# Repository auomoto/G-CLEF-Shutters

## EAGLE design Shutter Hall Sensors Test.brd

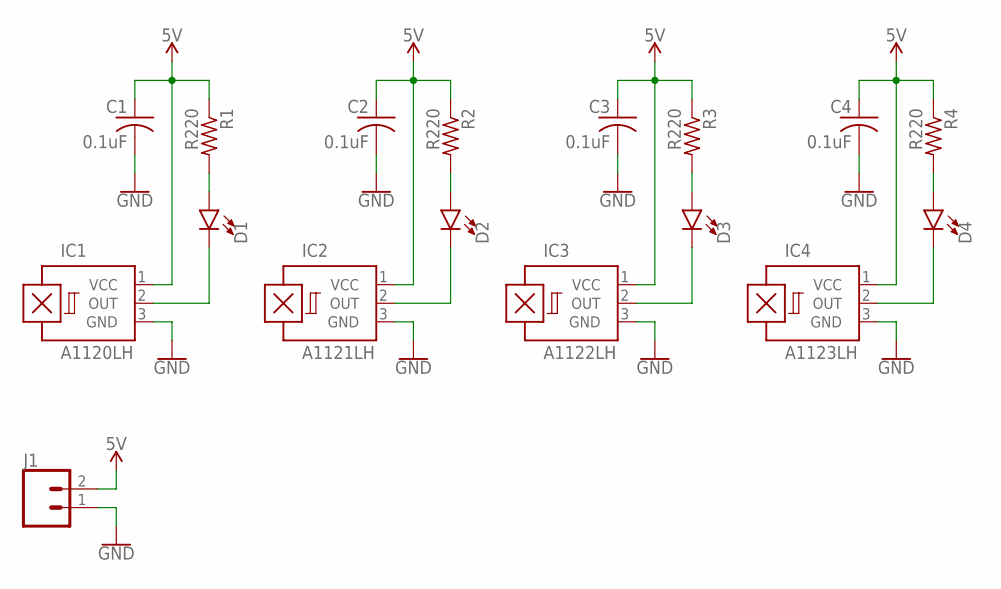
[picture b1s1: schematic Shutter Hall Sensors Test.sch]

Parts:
C1, C2, C3, C4: 0.1uF; C0805
D1, D2, D3, D4: LED5MM; LED_5MM
IC1: A1120LH; SOT23-W
IC2: A1121LH; SOT23-W
IC3: A1122LH; SOT23-W
IC4: A1123LH; SOT23-W
J1: CONN_02; 1X02
R1, R2, R3, R4: R220; R0805

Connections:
5V: C1.1, C2.1, C3.1, C4.1, IC1.1 (VCC), IC2.1 (VCC), IC3.1 (VCC), IC4.1 (VCC), J1.2, R1.1, R2.1, R3.1, R4.1
GND: C1.2, C2.2, C3.2, C4.2, IC1.3 (GND), IC2.3 (GND), IC3.3 (GND), IC4.3 (GND), J1.1
unnamed: D4.A, R4.2
unnamed: D3.K (C), IC3.2 (OUT)
unnamed: D4.K (C), IC4.2 (OUT)
unnamed: D1.A, R1.2
unnamed: D2.K (C), IC2.2 (OUT)
unnamed: D2.A, R2.2
unnamed: D1.K (C), IC1.2 (OUT)
unnamed: D3.A, R3.2

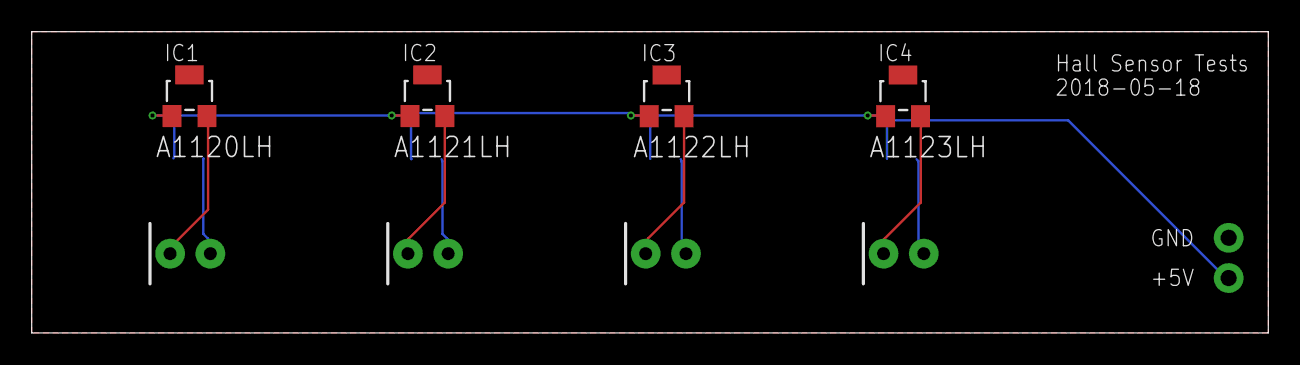
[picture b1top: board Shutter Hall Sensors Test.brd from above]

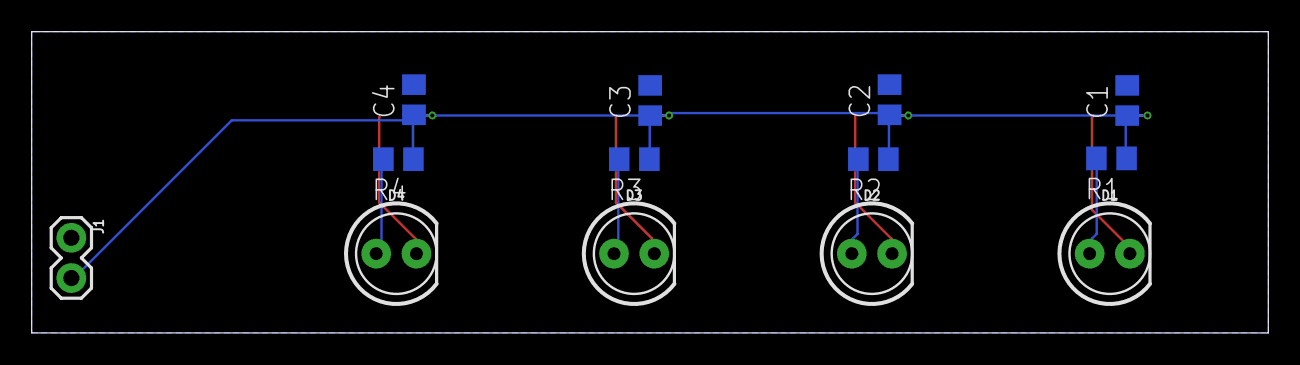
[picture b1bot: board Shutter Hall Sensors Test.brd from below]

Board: 2 copper layers, 78.0 x 19.0 mm, 17 parts (13 on the bottom side), 10 nets.

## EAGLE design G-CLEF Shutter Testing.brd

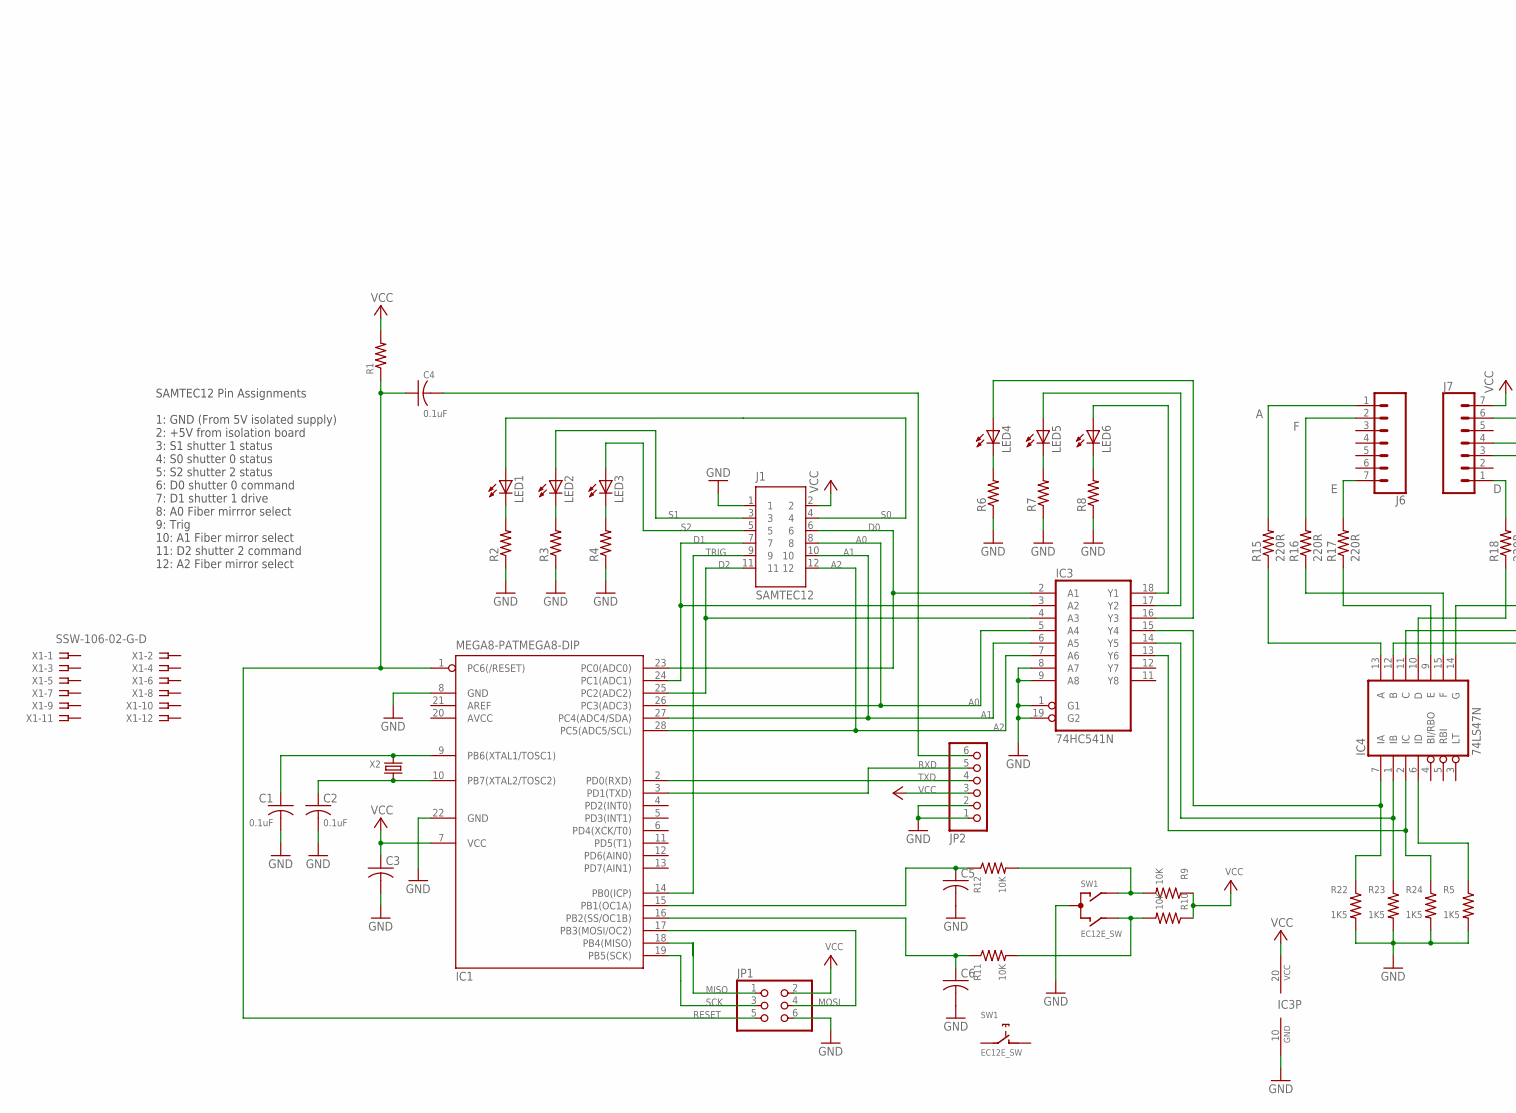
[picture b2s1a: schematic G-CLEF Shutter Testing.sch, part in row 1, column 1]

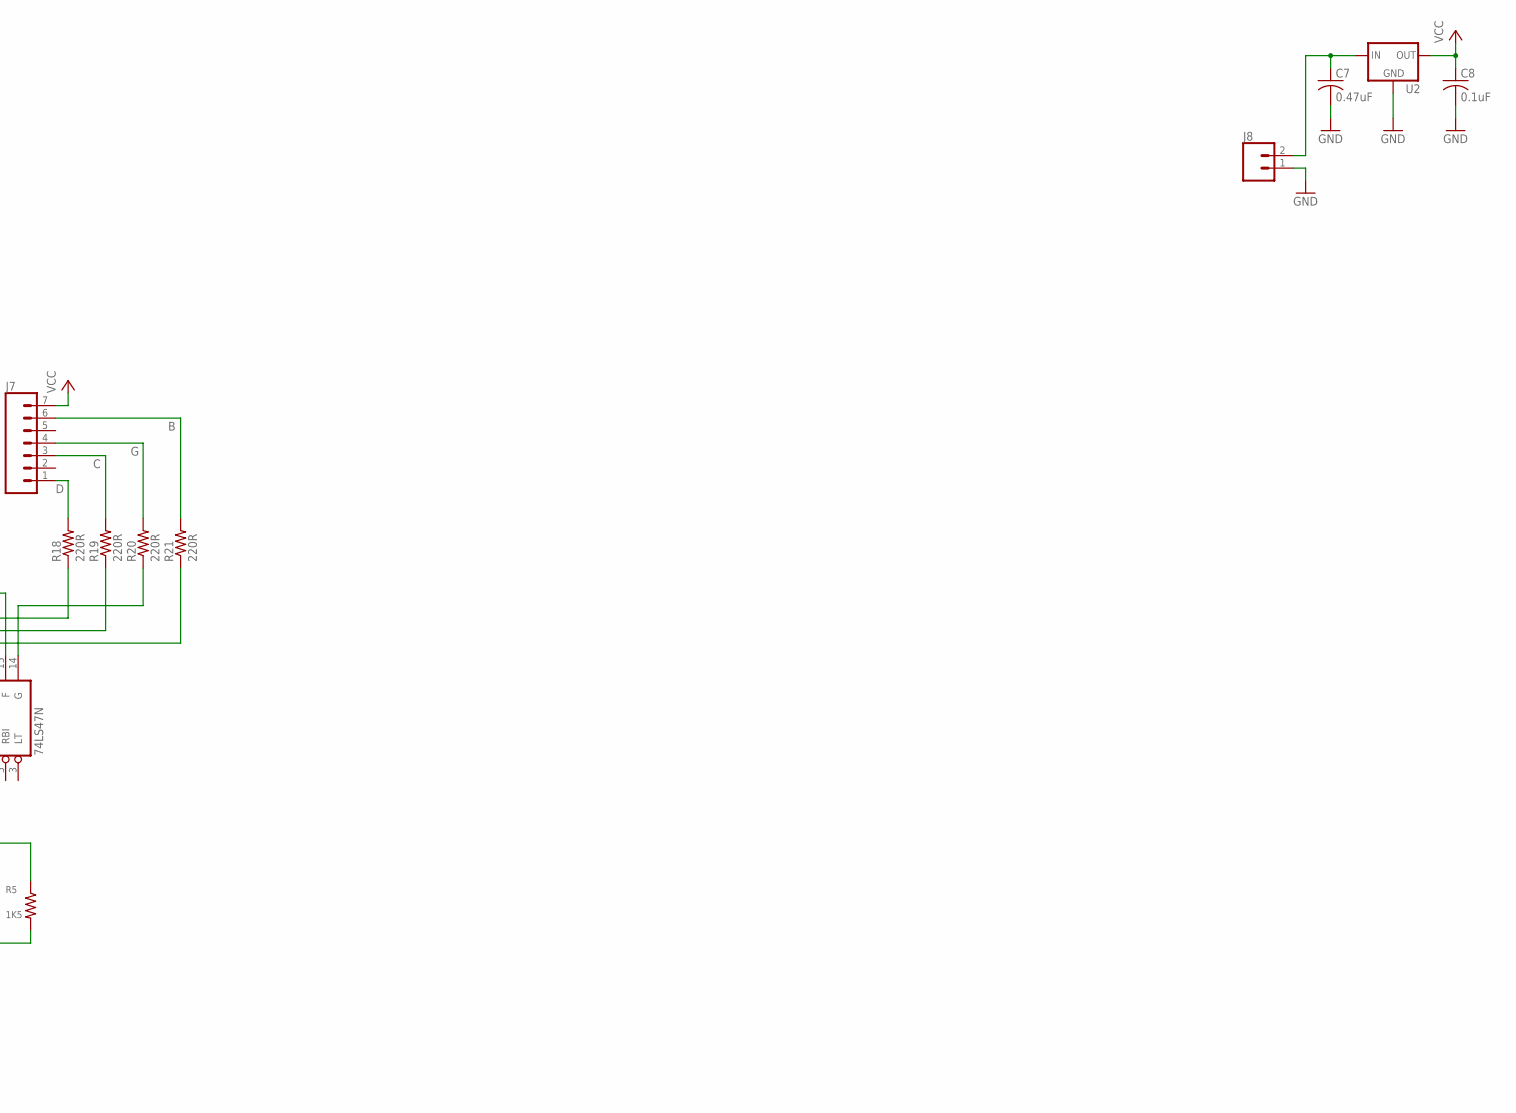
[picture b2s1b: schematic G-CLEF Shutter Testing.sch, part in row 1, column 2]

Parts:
C1, C2, C4: 0.1uF; C025-024X044
C3, C5, C6: C-US025-024X044; C025-024X044
C7: 0.47uF; C050-025X075
C8: 0.1uF; C050-025X075
IC1: MEGA8-PATMEGA8-DIP; DIP762W53P254L3467H457Q28B
IC3: 74HC541N; DIL20
IC4: 74LS47N; DIL16
J1: SAMTEC12
J6, J7: CONN_07; 1X07
J8: CONN_02; 1X02
JP1: PINHD-2X3; 2X03
JP2: PINHD-1X6/90; 1X06/90
LED1, LED2, LED3, LED4, LED5, LED6: LED5MM
R1, R2, R3, R4, R6, R7, R8: R-US_0207/7; 0207/7
R5, R22, R23, R24: 1K5; 0207/7
R9, R10, R11, R12: 10K; 0207/7
R15, R16, R17, R18, R19, R20, R21: 220R; 0207/7
SW1: EC12E_SW; ALPS_EC12E_SW
U2: V_REG_78XXSINK; TO220-IGO
X1: SSW-106-02-G-D
X2: CRYSTALS-NOGND-HC49; HC49

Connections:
A: J6.1, R15.2
A0: IC1.26 (PC3(ADC3)), IC3.5 (A4), J1.8
A1: IC1.27 (PC4(ADC4/SDA)), IC3.6 (A5), J1.10
A2: IC1.28 (PC5(ADC5/SCL)), IC3.7 (A6), J1.12
AVCC: IC1.20 (AVCC)
B: J7.6, R21.2
C: J7.3, R19.2
D: J7.1, R18.2
D0: IC1.23 (PC0(ADC0)), IC3.2 (A1), J1.6
D1: IC1.24 (PC1(ADC1)), IC3.3 (A2), J1.7
D2: IC1.25 (PC2(ADC2)), IC3.4 (A3), J1.11
E: J6.7, R17.2
F: J6.2, R16.2
G: J7.4, R20.2
GND: C1.2, C2.2, C3.2, C5.2, C6.2, C7.2, C8.2, IC1.8 (GND), IC1.22 (GND), IC3.1 (G1), IC3.8 (A7), IC3.9 (A8), IC3.10 (GND), IC3.19 (G2), IC4.8 (GND), J1.1, J8.1, JP1.6, JP2.1, JP2.2, R2.1, R3.1, R4.1, R5.2, R6.1, R7.1, R8.1, R22.2, R23.2, R24.2, SW1.C, U2.GND
MISO: IC1.18 (PB4(MISO)), JP1.1
MOSI: IC1.17 (PB3(MOSI/OC2)), JP1.4
unnamed: C1.1, IC1.9 (PB6(XTAL1/TOSC1)), X2.2
unnamed: C2.1, IC1.10 (PB7(XTAL2/TOSC2)), X2.1
unnamed: C4.2, JP2.6
unnamed: IC4.6 (ID), R5.1
unnamed: LED4.K (C), R6.2
unnamed: LED5.K (C), R7.2
unnamed: LED6.K (C), R8.2
unnamed: IC3.18 (Y1), LED6.A
unnamed: IC3.17 (Y2), LED5.A
unnamed: IC3.16 (Y3), LED4.A
unnamed: C5.1, IC1.15 (PB1(OC1A)), R12.1
unnamed: R9.2, R12.2, SW1.A
unnamed: R10.2, R11.2, SW1.B
unnamed: C6.1, IC1.16 (PB2(SS/OC1B)), R11.1
unnamed: LED1.K (C), R2.2
unnamed: LED2.K (C), R3.2
unnamed: LED3.K (C), R4.2
unnamed: IC4.13 (A), R15.1
unnamed: IC4.12 (B), R21.1
unnamed: IC4.11 (C), R19.1
unnamed: IC4.10 (D), R18.1
unnamed: IC4.9 (E), R17.1
unnamed: IC4.15 (F), R16.1
unnamed: IC4.14 (G), R20.1
unnamed: C7.1, J8.2, U2.IN
unnamed: IC3.13 (Y6), IC4.2 (IC), R24.1
unnamed: IC3.14 (Y5), IC4.1 (IB), R23.1
unnamed: IC3.15 (Y4), IC4.7 (IA), R22.1
RESET: C4.1, IC1.1 (PC6(/RESET)), JP1.5, R1.1
RXD: IC1.3 (PD1(TXD)), JP2.5
S0: J1.4, LED1.A
S1: J1.3, LED2.A
S2: J1.5, LED3.A
SCK: IC1.19 (PB5(SCK)), JP1.3
TRIG: IC1.14 (PB0(ICP)), J1.9
TXD: IC1.2 (PD0(RXD)), JP2.4
VCC: C3.1, C8.1, IC1.7 (VCC), IC3.20 (VCC), IC4.16 (VCC), J1.2, J7.7, JP1.2, JP2.3, R1.2, R9.1, R10.1, U2.OUT

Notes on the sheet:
SAMTEC12 Pin Assignments 1: GND (From 5V isolated supply) 2: +5V from isolation board 3: S1 shutter 1 status 4: S0 shutter 0 status 5: S2 shutter 2 status 6: D0 shutter 0 command 7: D1 shutter 1 drive 8: A0 Fiber mirrror select 9: Trig 10: A1 Fiber mirror select 11: D2 shutter 2 command 12: A2 Fibe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

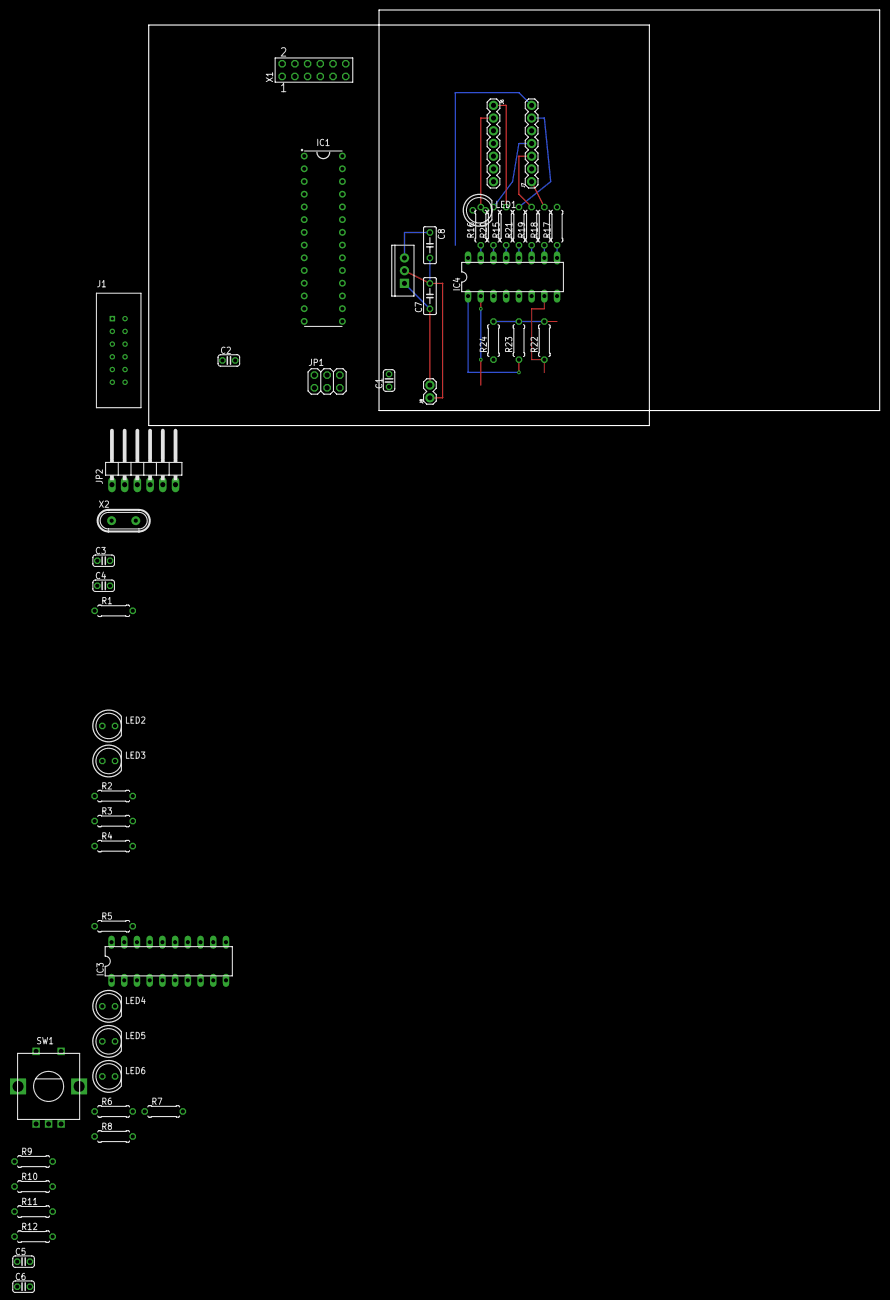
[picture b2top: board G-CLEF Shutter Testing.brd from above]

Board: 2 copper layers, 146.0 x 83.0 mm, 49 parts (0 on the bottom side), 53 nets.

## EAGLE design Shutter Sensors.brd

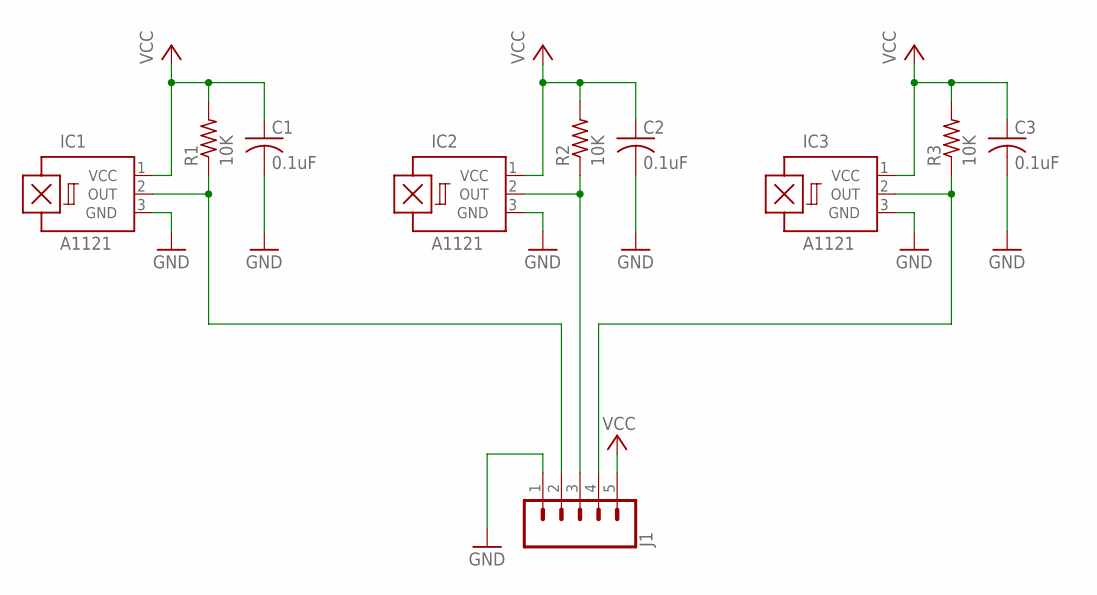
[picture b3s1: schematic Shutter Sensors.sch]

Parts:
C1, C2, C3: 0.1uF; C0805
IC1, IC2, IC3: A1121; SOT95P285X113-3
J1: CONN_051X05-0.1-RA; 1X05/90
R1, R2, R3: 10K; R0805

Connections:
GND: C1.2, C2.2, C3.2, IC1.3 (GND), IC2.3 (GND), IC3.3 (GND), J1.1
unnamed: IC2.2 (OUT), J1.3, R2.1
unnamed: IC1.2 (OUT), J1.2, R1.1
unnamed: IC3.2 (OUT), J1.4, R3.1
VCC: C1.1, C2.1, C3.1, IC1.1 (VCC), IC2.1 (VCC), IC3.1 (VCC), J1.5, R1.2, R2.2, R3.2

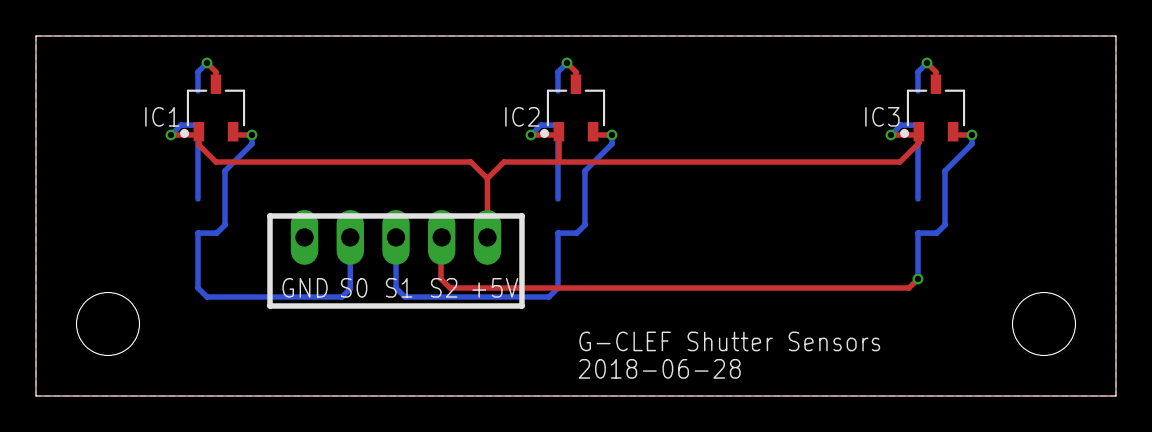
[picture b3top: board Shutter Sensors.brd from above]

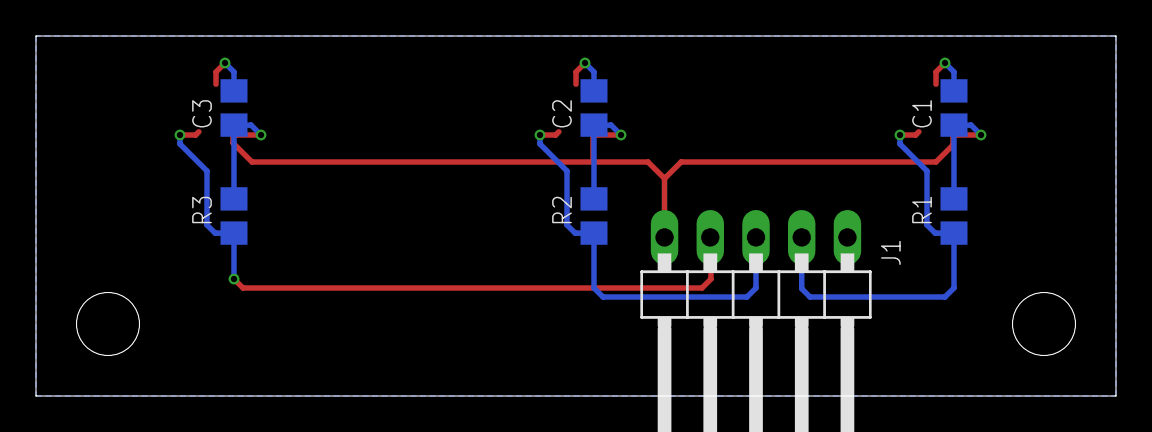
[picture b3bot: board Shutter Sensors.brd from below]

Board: 2 copper layers, 60.0 x 20.0 mm, 10 parts (7 on the bottom side), 5 nets.

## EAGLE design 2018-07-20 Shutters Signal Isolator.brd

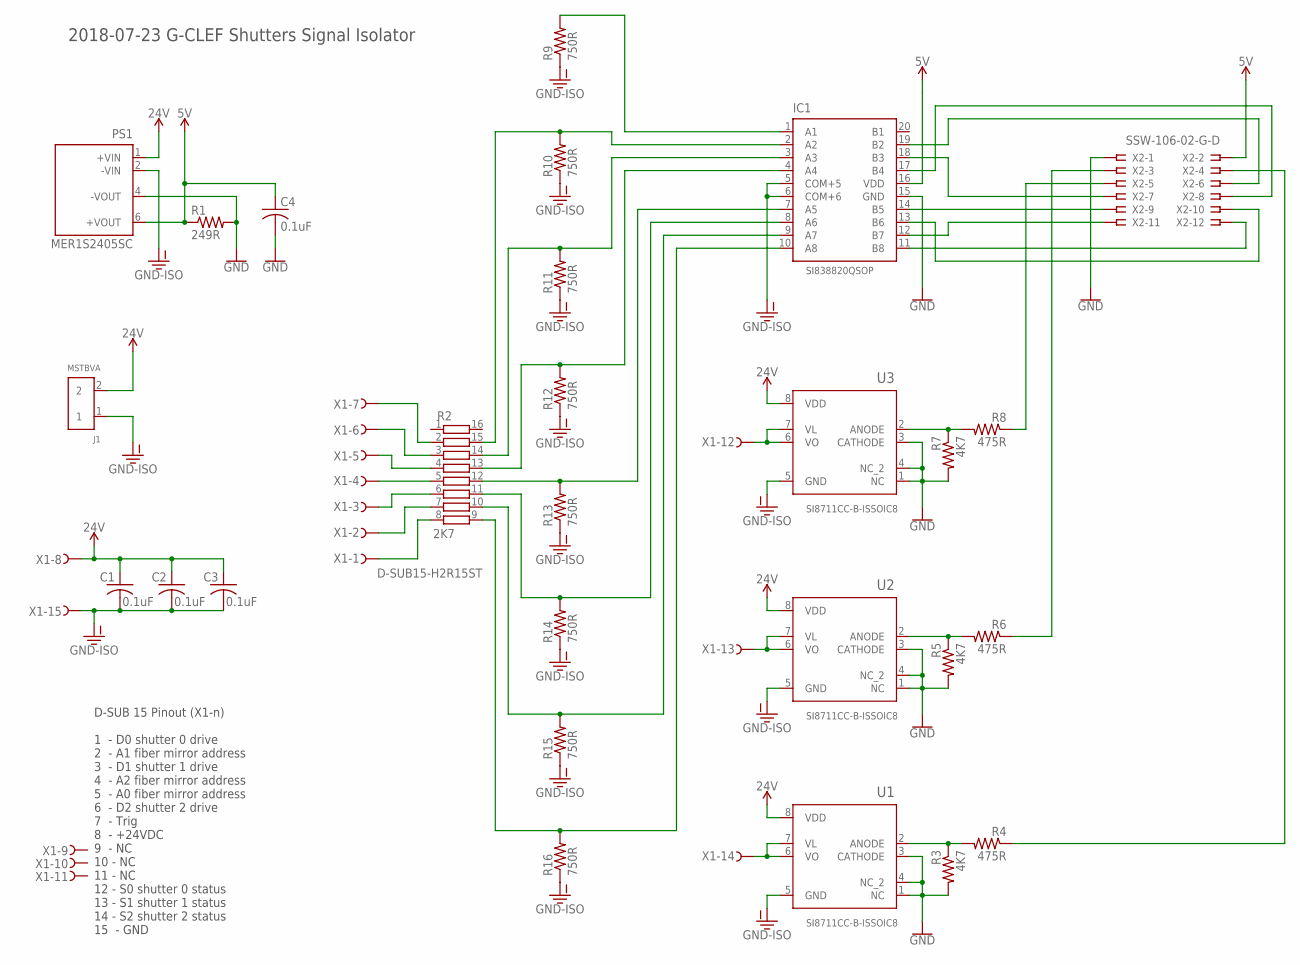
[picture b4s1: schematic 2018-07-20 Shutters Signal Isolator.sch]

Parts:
C1, C2, C3, C4: 0.1uF; C0805
IC1: SI838820QSOP; SOP63P600X175-20
J1: MSTBVA
PS1: MER1S2405SC; MER1
R1: 249R; R0805
R2: 2K7; SOIC127P765X227-16
R3, R5, R7: 4K7; R0805
R4, R6, R8: 475R; R0805
R9, R10, R11, R12, R13, R14, R15, R16: 750R; R0805
U1, U2, U3: SI8711CC-B-ISSOIC8; SOIC127P600X175-8
X1: D-SUB15-H2R15ST; H2R15ST
X2: SSW-106-02-G-D

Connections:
5V: C4.1, IC1.16 (VDD), PS1.6 (+VOUT), R1.1, X2.2
24V: C1.1, C2.1, C3.1, J1.2, PS1.1 (+VIN), U1.8 (VDD), U2.8 (VDD), U3.8 (VDD), X1.8
GND: C4.2, IC1.15 (GND), PS1.4 (-VOUT), R1.2, R3.2, R5.2, R7.2, U1.1 (NC), U1.3 (CATHODE), U1.4 (NC_2), U2.1 (NC), U2.3 (CATHODE), U2.4 (NC_2), U3.1 (NC), U3.3 (CATHODE), U3.4 (NC_2), X2.1
GND-ISO: C1.2, C2.2, C3.2, IC1.5 (COM+5), IC1.6 (COM+6), J1.1, PS1.2 (-VIN), R9.1, R10.1, R11.1, R12.1, R13.1, R14.1, R15.1, R16.1, U1.5 (GND), U2.5 (GND), U3.5 (GND), X1.15
unnamed: IC1.1 (A1), R9.2
unnamed: IC1.2 (A2), R2.15, R10.2
unnamed: IC1.11 (B8), X2.12
unnamed: IC1.12 (B7), X2.11
unnamed: IC1.3 (A3), R2.14, R11.2
unnamed: IC1.13 (B6), X2.10
unnamed: IC1.14 (B5), X2.9
unnamed: IC1.19 (B2), X2.6
unnamed: IC1.17 (B4), X2.8
unnamed: IC1.18 (B3), X2.7
unnamed: R2.8, X1.1
unnamed: IC1.4 (A4), R2.13, R12.2
unnamed: R2.7, X1.2
unnamed: IC1.7 (A5), R2.12, R13.2
unnamed: R2.6, X1.3
unnamed: IC1.8 (A6), R2.11, R14.2
unnamed: IC1.9 (A7), R2.10, R15.2
unnamed: IC1.10 (A8), R2.9, R16.2
unnamed: R2.5, X1.4
unnamed: R2.2, X1.7
unnamed: R2.3, X1.6
unnamed: R2.4, X1.5
unnamed: R6.1, X2.3
unnamed: R3.1, R4.2, U1.2 (ANODE)
unnamed: U1.6 (VO), U1.7 (VL), X1.14
unnamed: R5.1, R6.2, U2.2 (ANODE)
unnamed: U2.6 (VO), U2.7 (VL), X1.13
unnamed: R7.1, R8.2, U3.2 (ANODE)
unnamed: U3.6 (VO), U3.7 (VL), X1.12
S$0: R8.1, X2.5
S$2: R4.1, X2.4

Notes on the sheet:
D-SUB 15 Pinout (X1-n) 1 - D0 shutter 0 drive 2 - A1 fiber mirror address 3 - D1 shutter 1 drive 4 - A2 fiber mirror address 5 - A0 fiber mirror address 6 - D2 shutter 2 drive 7 - Trig 8 - +24VDC 9 - NC 10 - NC 11 - NC 12 - S0 shutter 0 status 13 - S1 shutter 1 status 14 - S2 shutter 2 status 15 - 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
2018-07-23 G-CLEF Shutters Signal Isolator

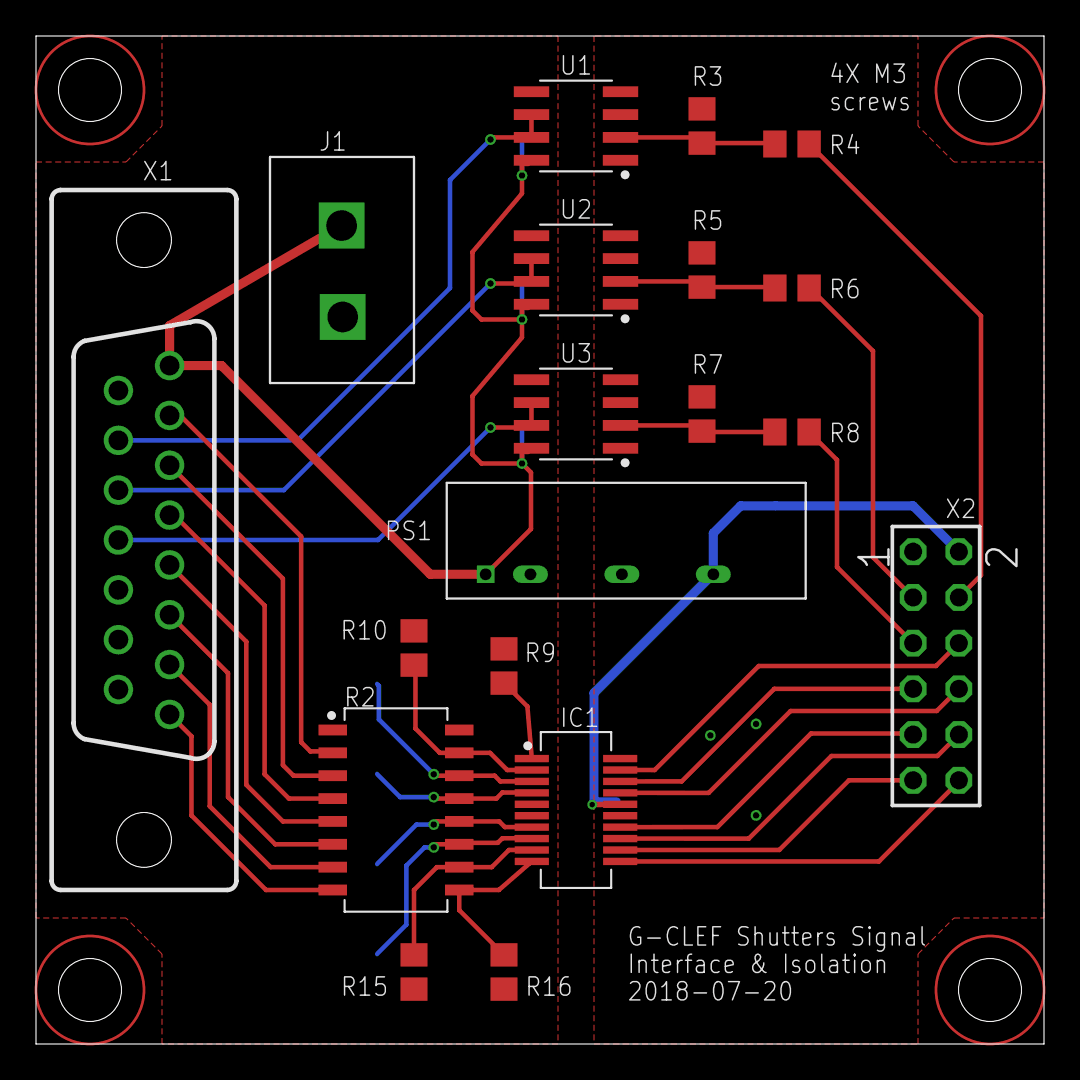
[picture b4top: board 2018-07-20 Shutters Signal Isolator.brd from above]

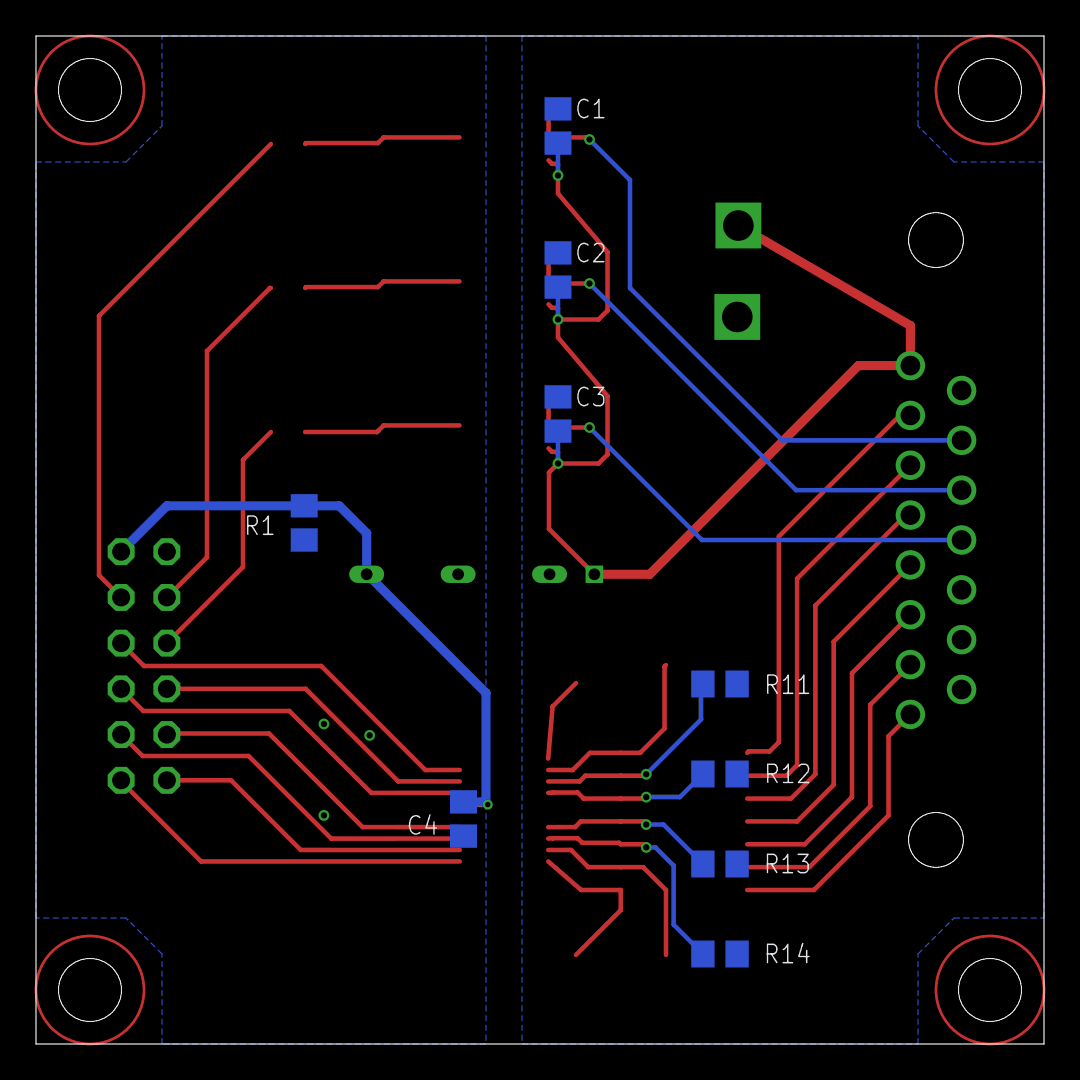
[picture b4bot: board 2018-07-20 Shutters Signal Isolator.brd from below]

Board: 2 copper layers, 56.0 x 56.0 mm, 28 parts (9 on the bottom side), 35 nets.

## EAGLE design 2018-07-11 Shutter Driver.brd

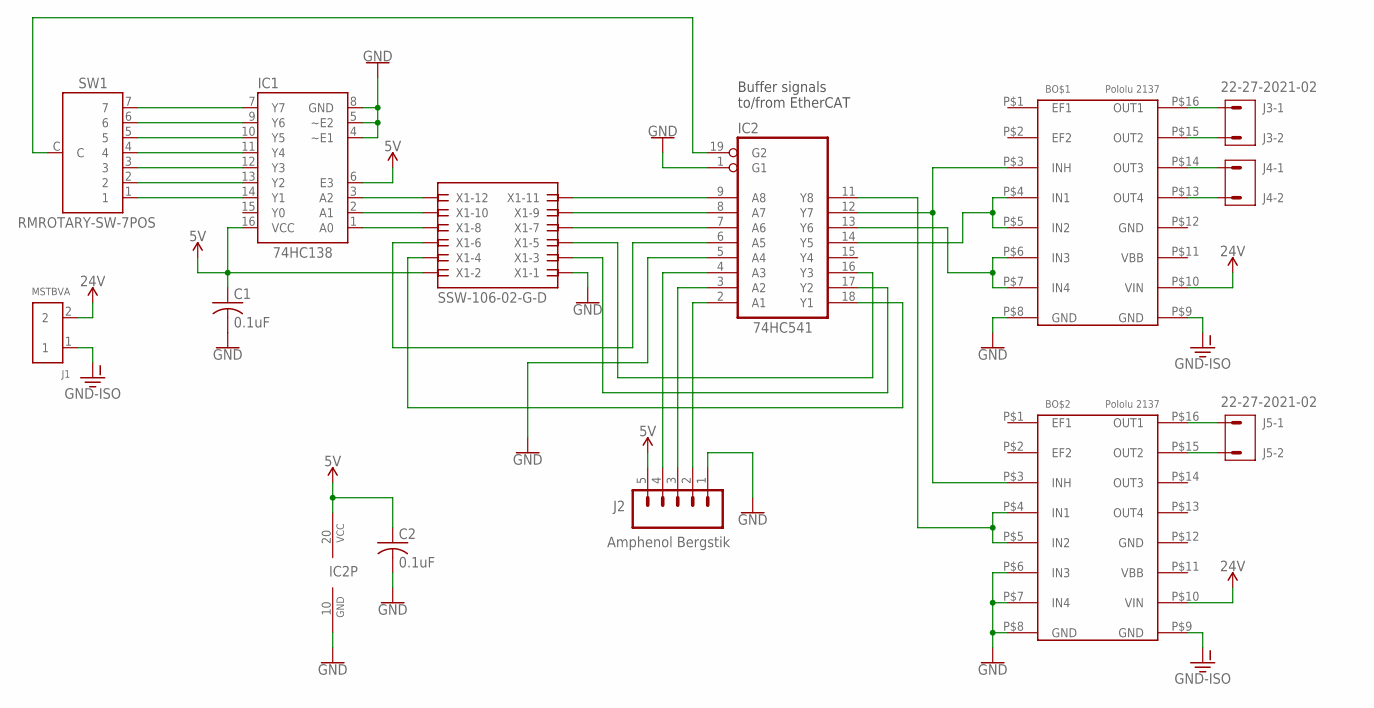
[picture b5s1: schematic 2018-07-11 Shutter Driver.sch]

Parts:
BO$1, BO$2: Pololu 2137; POLOLU2137
C1, C2: 0.1uF; C0805
IC1: 74HC138; SO16
IC2: 74HC541; SO20W
J1: MSTBVA
J2: Amphenol Bergstik; 1X05
J3, J4, J5: 22-27-2021-02; 6410-02
SW1: RMROTARY-SW-7POS
X1: SSW-106-02-G-D

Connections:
5V: C1.1, C2.1, IC1.6 (E3), IC1.16 (VCC), IC2.20 (VCC), J2.5, X1.2
24V: BO$1.P$10 (VIN), BO$2.P$10 (VIN), J1.2
GND: BO$1.P$8 (GND), BO$1.P$12 (GND), BO$2.P$6 (IN3), BO$2.P$7 (IN4), BO$2.P$8 (GND), BO$2.P$12 (GND), C1.2, C2.2, IC1.4 (~E1), IC1.5 (~E2), IC1.8 (GND), IC2.1 (G1), IC2.5 (A4), IC2.10 (GND), J2.1, X1.1
GND-ISO: BO$1.P$9 (GND), BO$2.P$9 (GND), J1.1
unnamed: BO$1.P$13 (OUT4), J4.2
unnamed: BO$1.P$14 (OUT3), J4.1
unnamed: IC1.12 (Y3), SW1.3
unnamed: BO$1.P$15 (OUT2), J3.2
unnamed: BO$1.P$16 (OUT1), J3.1
unnamed: IC1.11 (Y4), SW1.4
unnamed: IC1.10 (Y5), SW1.5
unnamed: IC1.9 (Y6), SW1.6
unnamed: IC1.7 (Y7), SW1.7
unnamed: IC1.14 (Y1), SW1.1
unnamed: BO$2.P$15 (OUT2), J5.2
unnamed: BO$2.P$16 (OUT1), J5.1
unnamed: IC1.13 (Y2), SW1.2
unnamed: IC1.3 (A2), X1.12
unnamed: IC1.2 (A1), X1.10
unnamed: IC1.1 (A0), X1.8
unnamed: IC2.8 (A7), X1.9
unnamed: IC2.7 (A6), X1.7
unnamed: IC2.2 (A1), J2.2
unnamed: IC2.6 (A5), X1.6
unnamed: IC2.3 (A2), J2.3
unnamed: IC2.4 (A3), J2.4
unnamed: IC2.16 (Y3), X1.5
unnamed: IC2.17 (Y2), X1.3
unnamed: IC2.18 (Y1), X1.4
unnamed: IC2.9 (A8), X1.11
unnamed: BO$1.P$6 (IN3), BO$1.P$7 (IN4), IC2.13 (Y6)
unnamed: BO$2.P$4 (IN1), BO$2.P$5 (IN2), IC2.11 (Y8)
unnamed: IC2.19 (G2), SW1.C
unnamed: BO$1.P$3 (INH), BO$2.P$3 (INH), IC2.12 (Y7)
unnamed: BO$1.P$4 (IN1), BO$1.P$5 (IN2), IC2.14 (Y5)

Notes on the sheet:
Buffer signals to/from EtherCAT

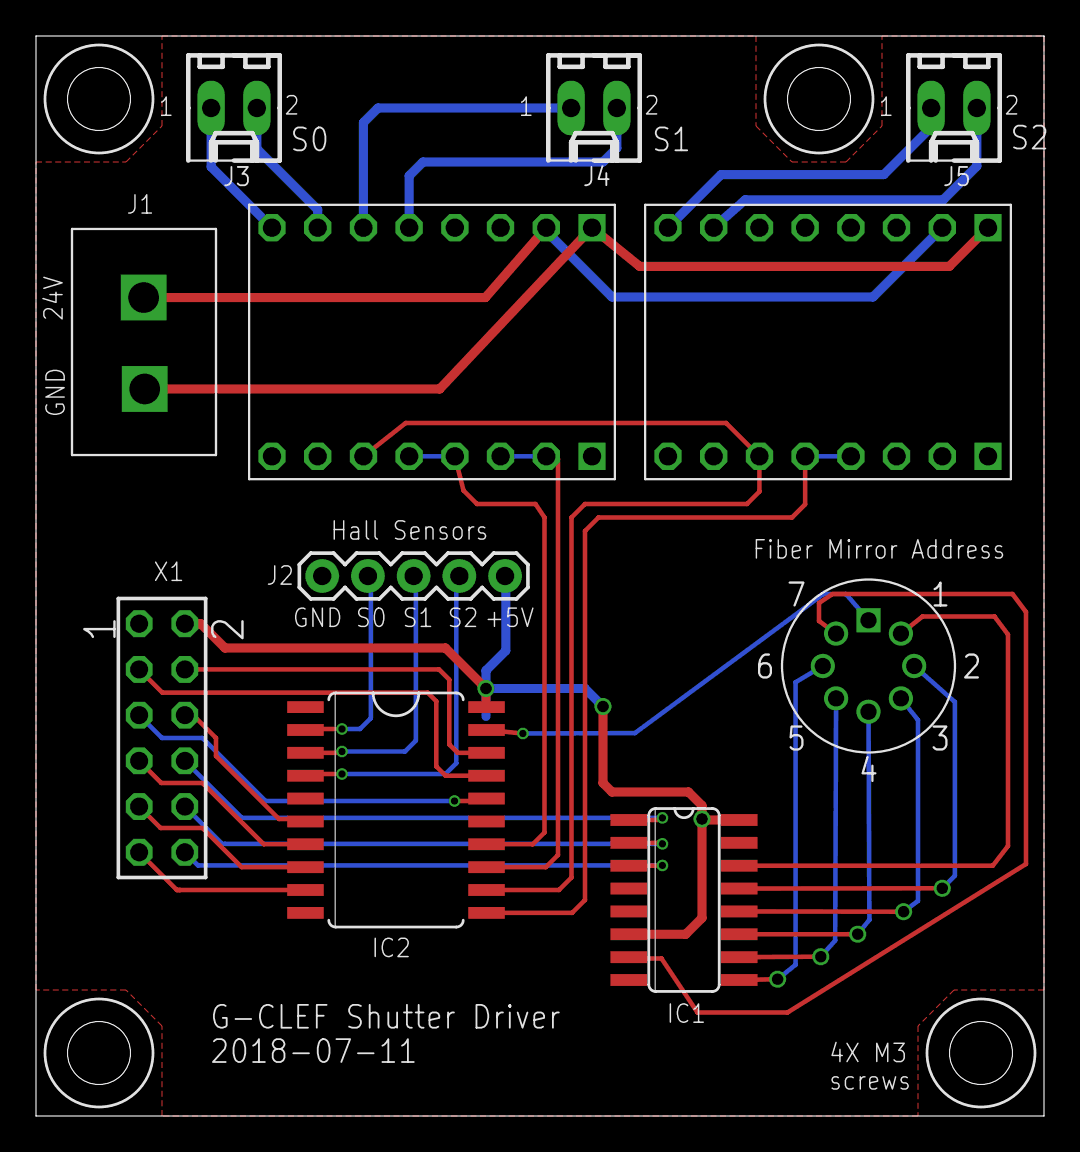
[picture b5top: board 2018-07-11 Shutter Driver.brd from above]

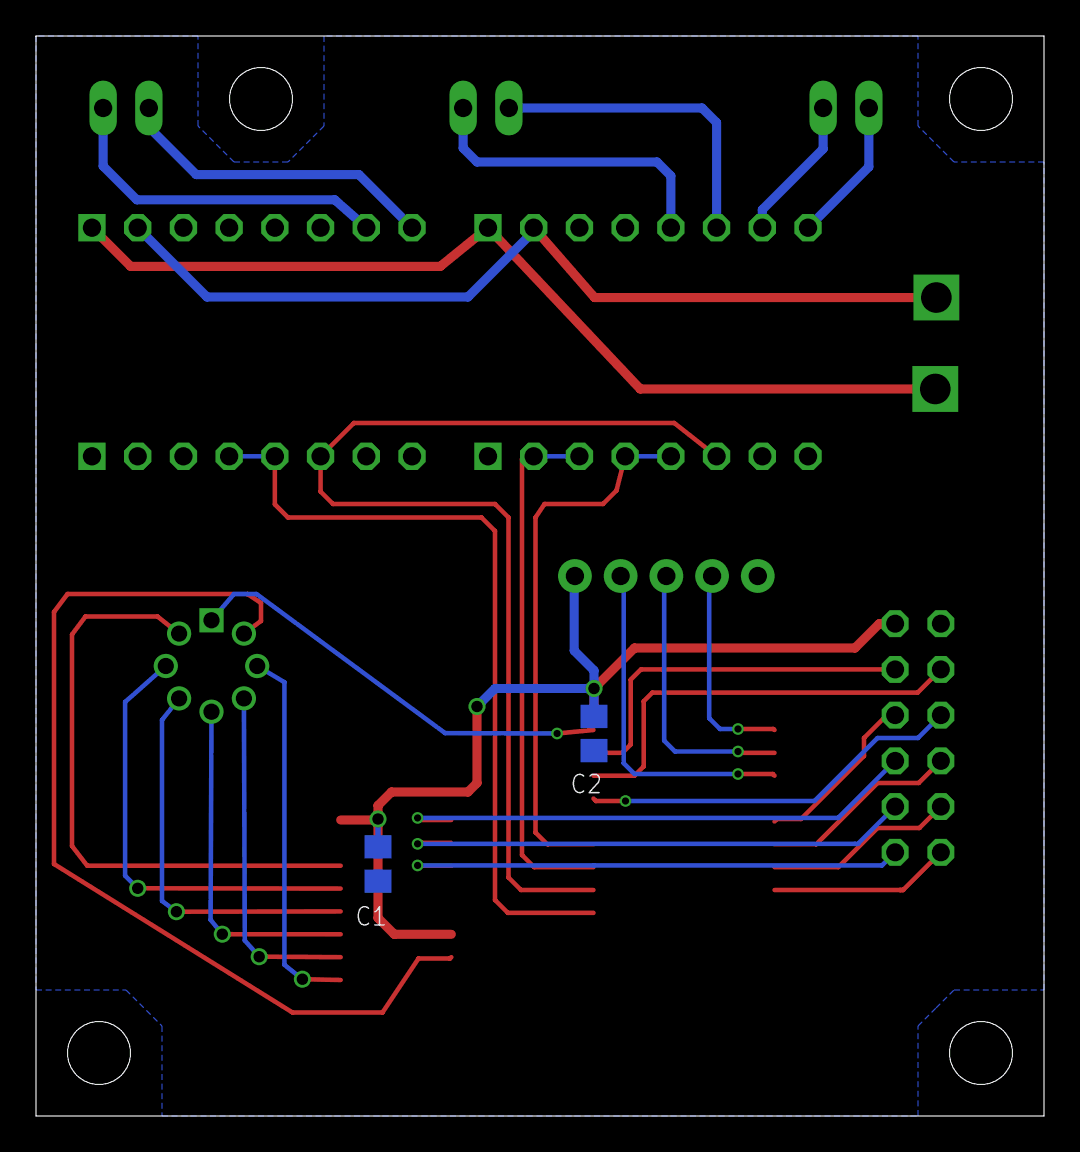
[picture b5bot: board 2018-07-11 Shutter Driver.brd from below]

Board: 2 copper layers, 56.0 x 60.0 mm, 13 parts (2 on the bottom side), 35 nets.

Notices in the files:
parts and their libraries:
SparkFun-Connectors: Licensing: Creative Commons ShareAlike 4.0 International - https://creativecommons.org/licenses/by-sa/4.0
